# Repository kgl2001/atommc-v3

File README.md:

# atommc3

Firmware for version 3+ boards.

Not to be mistaken for the utility ROM version, this is the firmware for the later board revisions.

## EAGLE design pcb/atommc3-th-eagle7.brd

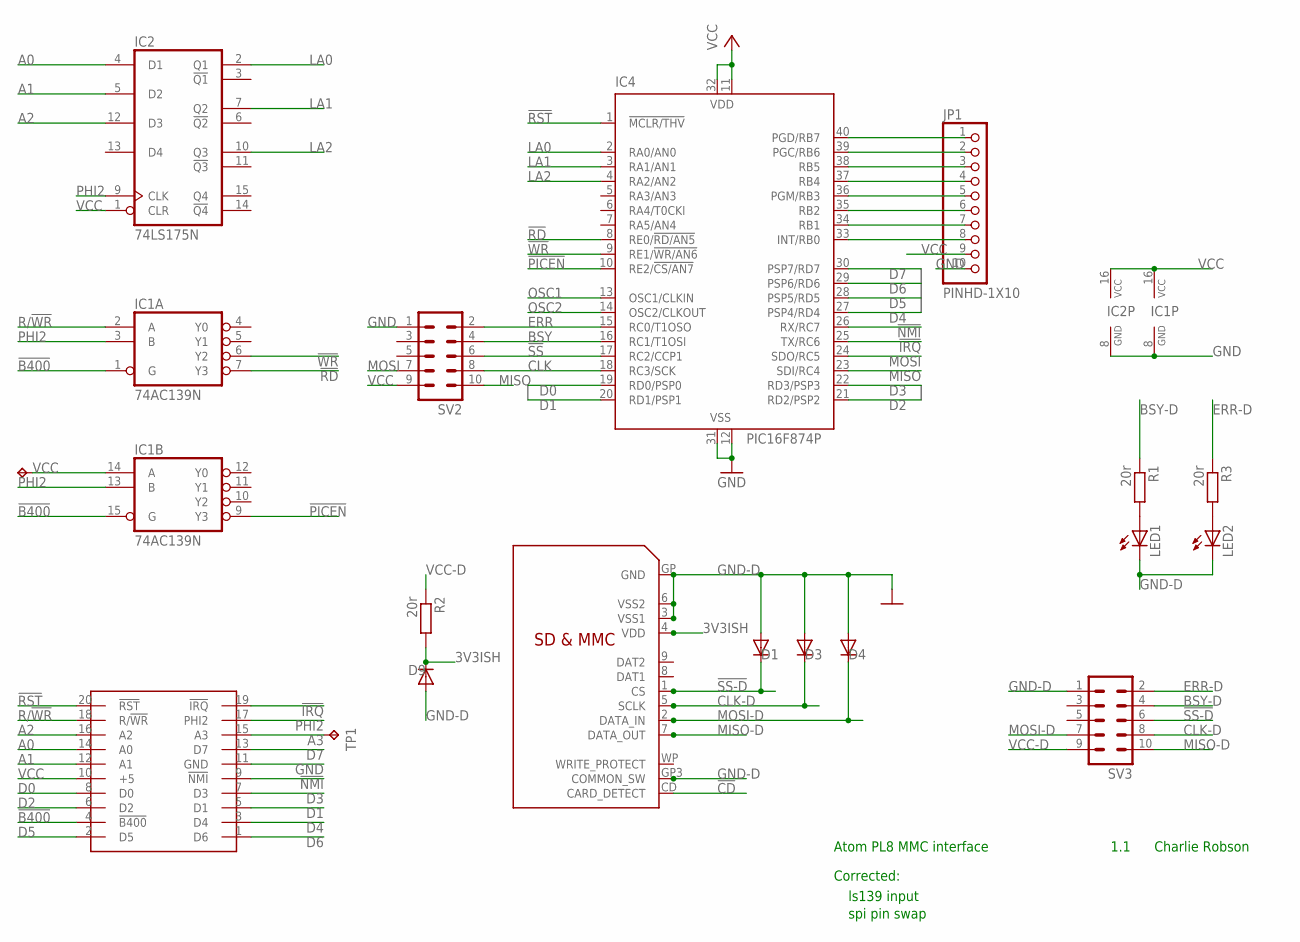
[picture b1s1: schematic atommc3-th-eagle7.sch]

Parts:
D1, D3, D4, D9: 3v3; DIODE_DO35-7
IC1: 74AC139N; DIL16
IC2: 74LS175N; DIL16
IC4: PIC16F874P; DIL40
JP1: PINHD-1X10; 1X10-BIG
LED1, LED2: LED3MM
R1, R2, R3: 20r; 0207/10
SV2, SV3: ML10
TP1, TP2: TPB1,27; B1,27
U$1: PL8-HEADER-MALE; HEADER-M
U$4: SDMMC06132-MOD; 06132-MOD

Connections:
3V3ISH: D9.C (A), R2.2, U$4.4 (VDD)
!B400: IC1.1 (G), IC1.15 (G), U$1.4 (!B400)
!CD: U$4.CD (CARD_DETECT)
!IRQ: IC4.25 (TX/RC6), U$1.19 (!IRQ)
!NMI: IC4.26 (RX/RC7), U$1.9 (!NMI)
!PICEN: IC1.9 (Y3), IC4.10 (RE2/!CS/AN7)
!RD: IC1.7 (Y3), IC4.8 (RE0/!RD/AN5)
!RST: IC4.1 (!MCLR/THV), U$1.20 (!RST)
!SS: IC4.17 (RC2/CCP1), SV2.6
!SS-D: D1.C (A), SV3.6, U$4.1 (CS)
!WR: IC1.6 (Y2), IC4.9 (RE1/!WR/AN6)
A0: IC2.4 (D1), U$1.14 (A0)
A1: IC2.5 (D2), U$1.12 (A1)
A2: IC2.12 (D3), U$1.16 (A2)
A3: TP1.TP, U$1.15 (A3)
BSY: IC4.16 (RC1/T1OSI), SV2.4
BSY-D: R1.1, SV3.4
CLK: IC4.18 (RC3/SCK), SV2.8
CLK-D: D3.C (A), SV3.8, U$4.5 (SCLK)
D0: IC4.19 (RD0/PSP0), U$1.8 (D0)
D1: IC4.20 (RD1/PSP1), U$1.5 (D1)
D2: IC4.21 (RD2/PSP2), U$1.6 (D2)
D3: IC4.22 (RD3/PSP3), U$1.7 (D3)
D4: IC4.27 (PSP4/RD4), U$1.3 (D4)
D5: IC4.28 (PSP5/RD5), U$1.2 (D5)
D6: IC4.29 (PSP6/RD6), U$1.1 (D6)
D7: IC4.30 (PSP7/RD7), U$1.13 (D7)
ERR: IC4.15 (RC0/T1OSO), SV2.2
ERR-D: R3.1, SV3.2
GND: IC1.8 (GND), IC2.8 (GND), IC4.12 (VSS), IC4.31 (VSS), JP1.10, SV2.1, U$1.11 (GND)
GND-D: D1.A (C), D3.A (C), D4.A (C), D9.A (C), LED1.K (C), LED2.K (C), SV3.1, U$4.3 (VSS1), U$4.6 (VSS2), U$4.GP (GND), U$4.GP3 (COMMON_SW)
LA0: IC2.2 (Q1), IC4.2 (RA0/AN0)
LA1: IC2.7 (Q2), IC4.3 (RA1/AN1)
LA2: IC2.10 (Q3), IC4.4 (RA2/AN2)
MISO: IC4.23 (SDI/RC4), SV2.10
MISO-D: SV3.10, U$4.7 (DATA_OUT)
MOSI: IC4.24 (SDO/RC5), SV2.7
MOSI-D: D4.C (A), SV3.7, U$4.2 (DATA_IN)
unnamed: IC4.40 (PGD/RB7), JP1.1
unnamed: IC4.39 (PGC/RB6), JP1.2
unnamed: IC4.38 (RB5), JP1.3
unnamed: IC4.37 (RB4), JP1.4
unnamed: IC4.36 (PGM/RB3), JP1.5
unnamed: IC4.35 (RB2), JP1.6
unnamed: IC4.34 (RB1), JP1.7
unnamed: IC4.33 (INT/RB0), JP1.8
unnamed: LED1.A, R1.2
unnamed: LED2.A, R3.2
OSC1: IC4.13 (OSC1/CLKIN)
OSC2: IC4.14 (OSC2/CLKOUT)
PHI2: IC1.3 (B), IC1.13 (B), IC2.9 (CLK), U$1.17 (PHI2)
R/!WR: IC1.2 (A), U$1.18 (R/!WR)
VCC: IC1.14 (A), IC1.16 (VCC), IC2.1 (CLR), IC2.16 (VCC), IC4.11 (VDD), IC4.32 (VDD), JP1.9, SV2.9, TP2.TP, U$1.10 (+5)
VCC-D: R2.1, SV3.9

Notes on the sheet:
Atom PL8 MMC interface
Charlie Robson
1.1
Corrected:
ls139 input
spi pin swap

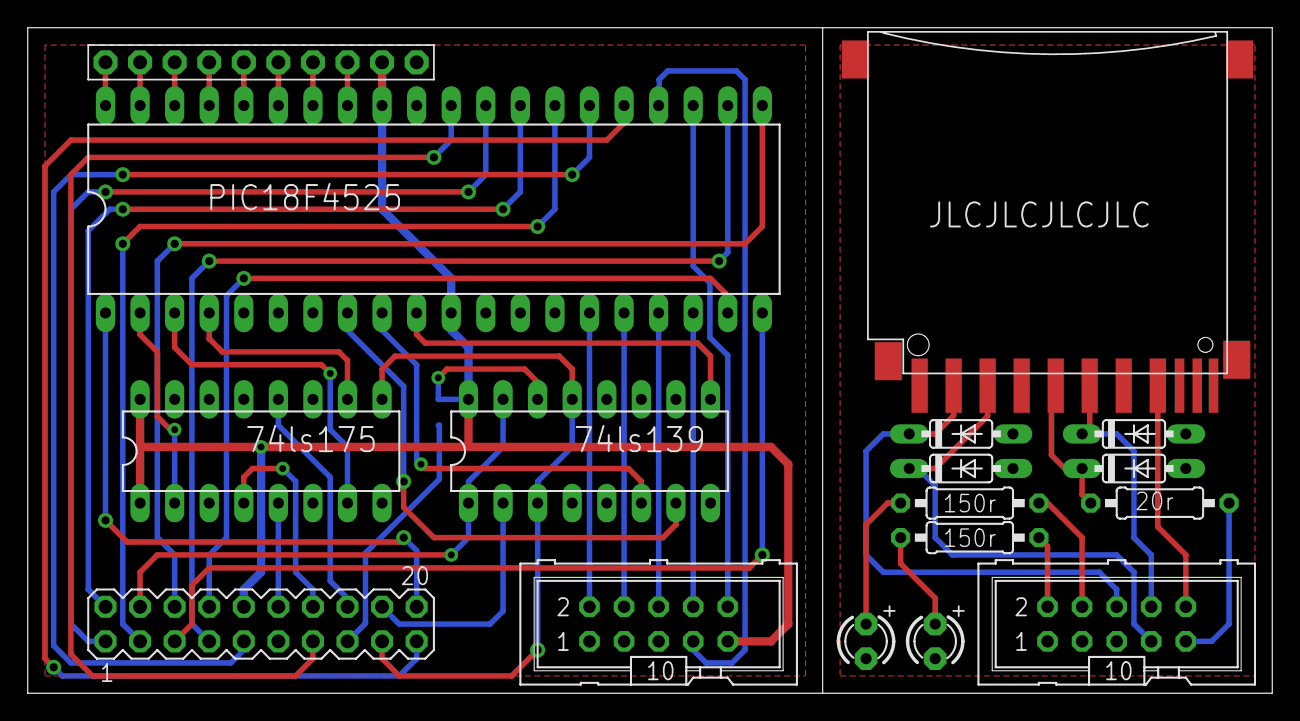
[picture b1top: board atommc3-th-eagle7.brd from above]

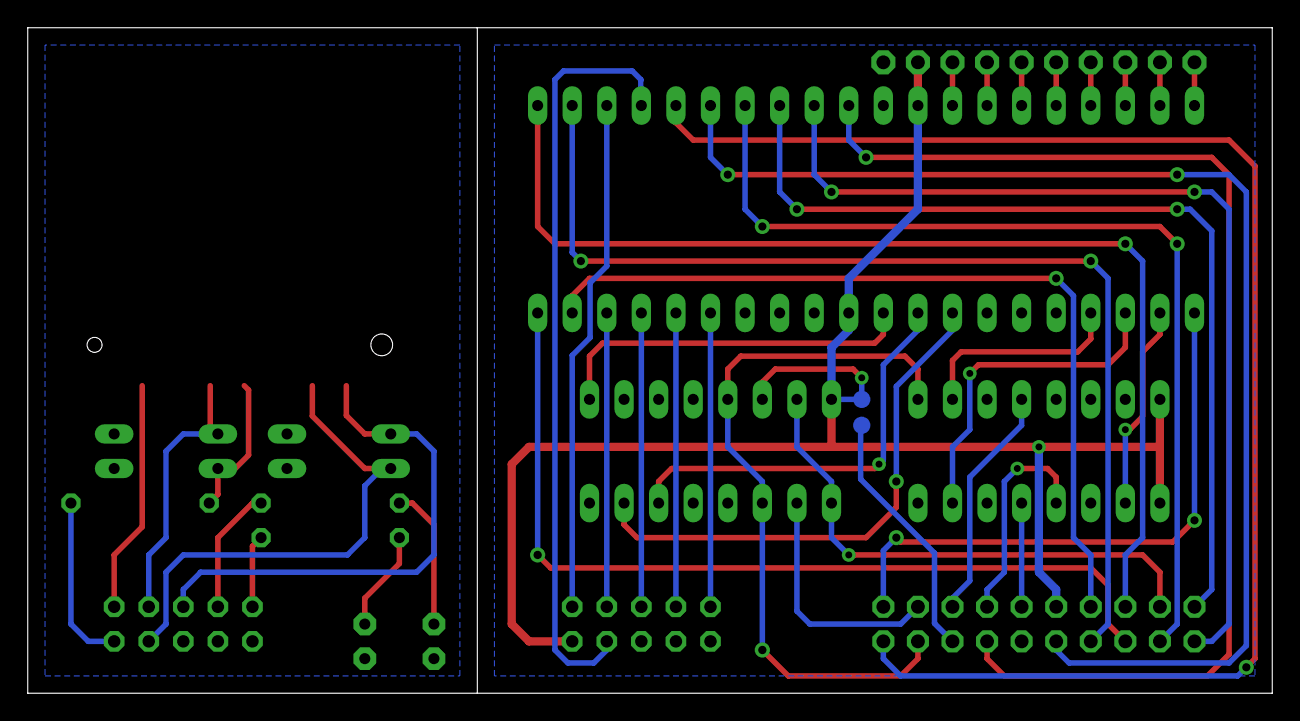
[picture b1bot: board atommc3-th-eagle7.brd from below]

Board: 2 copper layers, 91.4 x 48.9 mm, 19 parts (2 on the bottom side), 51 nets.

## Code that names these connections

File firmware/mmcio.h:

#ifndef _MMC

#include "integer.h"

#define SPI_CS_PIN PORTCbits.RC2
#define SPI_CS_TRIS TRISCbits.TRISC2

#define SPI_SCK_PIN PORTCbits.RC3
#define SPI_SCK_TRIS TRISCbits.TRISC3

#define SPI_DIN_PIN PORTCbits.RC4
#define SPI_DIN_TRIS TRISCbits.TRISC4

#define SPI_DOUT_PIN PORTCbits.RC5
#define SPI_DOUT_TRIS TRISCbits.TRISC5

#define SELECT()   SPI_CS_PIN=0
#define DESELECT() SPI_CS_PIN=1
#define MMC_SEL()  SPI_CS_PIN==0

/* Card type flags (CardType) */
#define CT_MMC 0x01 /* MMC ver 3 */
#define CT_SD1 0x02 /* SD ver 1 */
#define CT_SD2 0x04 /* SD ver 2 */
#define CT_SDC (CT_SD1|CT_SD2) /* SD */
#define CT_BLOCK 0x08 /* Block addressing */

#define _MMC
#endif

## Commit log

2021-01-01 rebuilding from ground up
2021-01-02 refactor to v3 codebase, working
2021-01-02 add burn script
2021-01-02 adding IRQ mod for VB4 hardware
2021-01-03 remove ds store
2023-01-26 Added #DEFINE to enable build for either V3 or V4 hardware
